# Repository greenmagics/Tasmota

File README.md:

# Tasmota
 Tasmota Serial to MQTT

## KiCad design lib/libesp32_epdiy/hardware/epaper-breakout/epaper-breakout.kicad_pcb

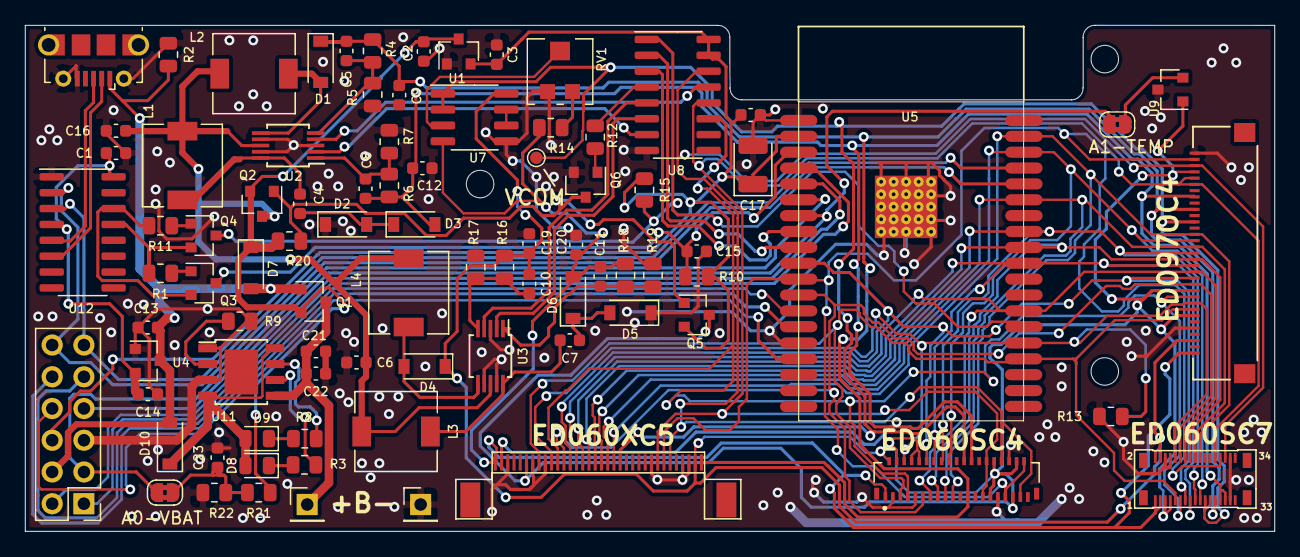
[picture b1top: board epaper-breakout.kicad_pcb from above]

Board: 2 copper layers, 100.0 x 40.5 mm, 90 parts (0 on the bottom side), 75 nets.

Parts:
C1, C6: 4.7uF; C_0603_1608Metric
C2, C3, C21: 10uF; C_0603_1608Metric
C4, C7, C15, C16, C22, C23: 0.1uF; C_0603_1608Metric
C5, C10: 4.7pF; C_0603_1608Metric
C8, C11: 100pF; C_0603_1608Metric
C9, C12, C13, C14, C18, C19, C20: 1uF; C_0603_1608Metric
C17: 100uF; CP_EIA-3528-15_AVX-H
D1, D2, D3, D4, D5, D6: MBR0540; D_SOD-123
D7, D10: 1N5817; D_SOD-123
D8: LED GREEN; LED_0805_2012Metric
D9: LED RED; LED_0805_2012Metric
H1, H2, H3: MountingHole; MountingHole_2.2mm_M2
J1: XF2M-3315-1A; CONN_ED097OC4
J2: C10418; USB_Micro-B_A01SB141B1-067
J3: Conn_02x06_Counter_Clockwise; PinHeader_2x06_P2.54mm_Vertical
J4: ED060SC4; HRS_FH26W-39S-0.3SHW(60)
J5, J6: Conn_01x01_Male; PinHeader_1x01_P2.54mm_Vertical
JP_BAT1: Jumper; SolderJumper-2_P1.3mm_Bridged2Bar_RoundedPad1.0x1.5mm
JP_TEMP1: Jumper; SolderJumper-2_P1.3mm_Bridged2Bar_RoundedPad1.0x1.5mm
L1, L2, L3, L4: 22uH; L_6.3x6.3_H3
Q1, Q2, Q5: AO3401A; SOT-23
Q3, Q4, Q6: MMBT3904; SOT-23
R1, R10, R11, R13, R15, R19, R20: 10k; R_0805_2012Metric
R2: 100k; R_0805_2012Metric
R3, R8, R12: 1k; R_0805_2012Metric
R4: 2M; R_0805_2012Metric
R5: 120k; R_0805_2012Metric
R6: 560k; R_0805_2012Metric
R7: 39k; R_0805_2012Metric
R9: 6.8k; R_0805_2012Metric
R14: 390k; R_0805_2012Metric
R16: 300k; R_0805_2012Metric
R17: 27k; R_0805_2012Metric
R18: 110k; R_0805_2012Metric
R21: 680k; R_0805_2012Metric
R22: 150k; R_0805_2012Metric
RV1: 200k; EVM3ESX50B25
TP1: TestPoint_Probe; TestPoint_Pad_D1.0mm
U1: MCP1700-3302E_SOT23; SOT-23
U2, U3: LT1945; MSOP-10_3x3mm_P0.5mm
U4: XC6206PxxxMR; SOT-23
U5: ESP32-WROVER
U6: ED060XC5; X05A20H34G
U7: LM358; SOP-8_3.76x4.96mm_P1.27mm
U8: 74HC4094-normal; SOIC-16_3.9x9.9mm_P1.27mm
U9: MCP9700AT-ETT; SOT-23
U10: ED060SC7; AXT334124
U11: TP4056; TP4056_SOP-8-PP
U12: CH340C; SOIC-16_3.9x9.9mm_P1.27mm

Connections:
/15V: C10.2, C19.2, D4.1, J1.3, J4.2, R16.1, U6.33, U7.8, U10.2, U10.4
/+3.3V: C3.2, C17.1, C18.2, J3.6, Q5.2, R10.1, R15.1, U1.2, U5.2, U8.15, U8.16
/+3.3_Serial: C14.2, C16.1, U4.2, U12.4, U12.16
/+22V: C5.2, C9.2, D1.1, J1.24, J4.23, R4.1, U6.34, U10.25
/-15V: C11.2, C20.2, D6.2, J1.1, J4.1, R14.1, R18.1, U6.1, U7.4, U10.1, U10.3
/-20V: C8.2, C12.2, D3.2, J1.26, J4.24, R6.1, U6.2, U10.27, U10.29
/A0: J3.3, JP_BAT1.1, U5.6
/A1: J3.7, JP_TEMP1.2, U5.7
/CTRL+15V: U3.4, U8.5
/CTRL+22V: U2.4, U8.13
/CTRL-15V: U3.2, U8.6
/CTRL-20V: U2.2, U8.7
/EN: C15.1, Q3.3, R10.2, U5.3
/EP_CKH: J1.8, J4.5, U5.23, U6.8, U10.9
/EP_CKV: J1.32, J4.33, J4.38, U5.11, U6.28, U10.28
/EP_D0: J1.13, J4.12, U5.10, U6.13, U10.13
/EP_D1: J1.14, J4.13, U5.26, U6.14, U10.14
/EP_D2: J1.15, J4.14, U5.29, U6.15, U10.15
/EP_D3: J1.16, J4.15, U5.30, U6.16, U10.16
/EP_D4: J1.17, J4.16, U5.31, U6.17, U10.17
/EP_D5: J1.18, J4.17, U5.33, U6.18, U10.18
/EP_D6: J1.19, J4.18, U5.36, U6.19, U10.19
/EP_D7: J1.20, J4.19, U5.37, U6.20, U10.20
/EP_LE: J1.9, J4.6, R13.1, U5.24, U6.10, U10.10
/EP_MODE: J1.28, J1.29, J4.27, J4.28, U6.27, U8.12, U10.26
/EP_OE: J1.10, J4.7, U6.11, U8.11, U10.11
/EP_STH: J1.12, J4.11, U5.12, U6.12, U10.12
/EP_STV: J1.31, J4.32, J4.37, U6.29, U8.14, U10.30
/EP_VCOM: J1.22, J4.22, TP1.1, U6.21, U7.1, U7.2, U10.21, U10.23
/IO0: Q4.3, R15.2, U5.25, U8.1
/MISO: J3.10, U5.14
/MOSI: J3.8, U5.16
/SCLK: J3.9, U5.13
/SENSOR_VN: J3.2, U5.5
/SENSOR_VP: J3.1, U5.4
/SMPS_CTRL: R12.2, U8.4
/USB_RXD: J3.11, U5.35, U12.3
/USB_TXD: J3.12, U5.34, U12.2
/~DTR: Q4.2, R1.2, U12.13
/~RTS: Q3.2, R11.2, U12.14
BAT+: C21.1, C22.2, J5.1, Q1.3, U11.5
EPD_VDD: J1.7, J1.11, J1.30, J4.4, J4.8, J4.10, J4.29, J4.30, J4.35, J4.36, Q5.3, U6.6, U9.1, U10.5, U10.7
GND: C1.2, C2.1, C3.1, C6.2, C9.1, C12.1, C13.2, C14.1, C15.2, C16.2, C17.2, C18.1, C19.1, C20.1, C21.2, C22.1, C23.1, D2.1, D5.1, J1.5, J1.33, J2.5, J2.6, J3.5, J4.3, J4.9, J4.31, J4.34, J6.1, Q6.2, R2.1, R5.2, R7.2, R9.1, R13.2, R17.2, R19.2, R22.2, RV1.1, U1.1, U2.3, U2.7, U2.9, U3.3, U3.7, U3.9, U4.1, U5.1, U5.15, U5.38, U5.39, U6.3, U6.7, U6.9, U6.26, U6.31, U6.32, U7.5, U8.8, U9.3, U10.6, U10.8, U10.31, U10.32, U11.1, U11.3, U12.1
unnamed: C4.1, D2.2, D3.1
unnamed: C4.2, L1.1, U2.10
unnamed: C5.1, R4.2, R5.1, U2.5
unnamed: C7.1, D5.2, D6.1
unnamed: C7.2, L3.1, U3.10
unnamed: C8.1, R6.2, R7.1, U2.1
unnamed: C10.1, R16.2, R17.1, U3.5
unnamed: C11.1, R18.2, R19.1, U3.1
unnamed: C23.2, JP_BAT1.2, R21.2, R22.1
unnamed: D1.2, L2.1, U2.6
unnamed: D4.2, L4.1, U3.6
unnamed: D8.1, R3.2
unnamed: D9.1, R8.2
unnamed: D8.2, D9.2, D10.1, U11.4, U11.8
unnamed: J2.2, U12.6
unnamed: J2.3, U12.5
unnamed: JP_TEMP1.1, U9.2
unnamed: Q2.1, Q5.1, Q6.3, R20.1
unnamed: Q3.1, R1.1
unnamed: Q4.1, R11.1
unnamed: Q6.1, R12.1
unnamed: R3.1, U11.6
unnamed: R8.1, U11.7
unnamed: R9.2, U11.2
unnamed: R14.2, RV1.3
unnamed: RV1.2, U7.3
unnamed: U5.8, U8.3
unnamed: U5.9, U8.2
unnamed: U7.6, U7.7
SW_VIN: C1.1, C6.1, L1.2, L2.2, L3.2, L4.2, Q2.3, U2.8, U3.8
VBUS: C13.1, D7.2, D10.2, J2.1, J3.4, Q1.1, R2.2, U4.3
VIN: C2.2, D7.1, Q1.2, Q2.2, R20.2, R21.1, U1.3

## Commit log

2021-09-30 Dodano pliki z repozytorium
2021-09-30 Dodano podstawowe ustawienia

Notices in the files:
parts and their libraries:
Copyright 2016 Accelerated Designs. All rights reserved.
